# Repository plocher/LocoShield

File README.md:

# LocoShield
## License: CERN Open Hardware Licence v1.2

An electrical interface to Digitrax Loconet

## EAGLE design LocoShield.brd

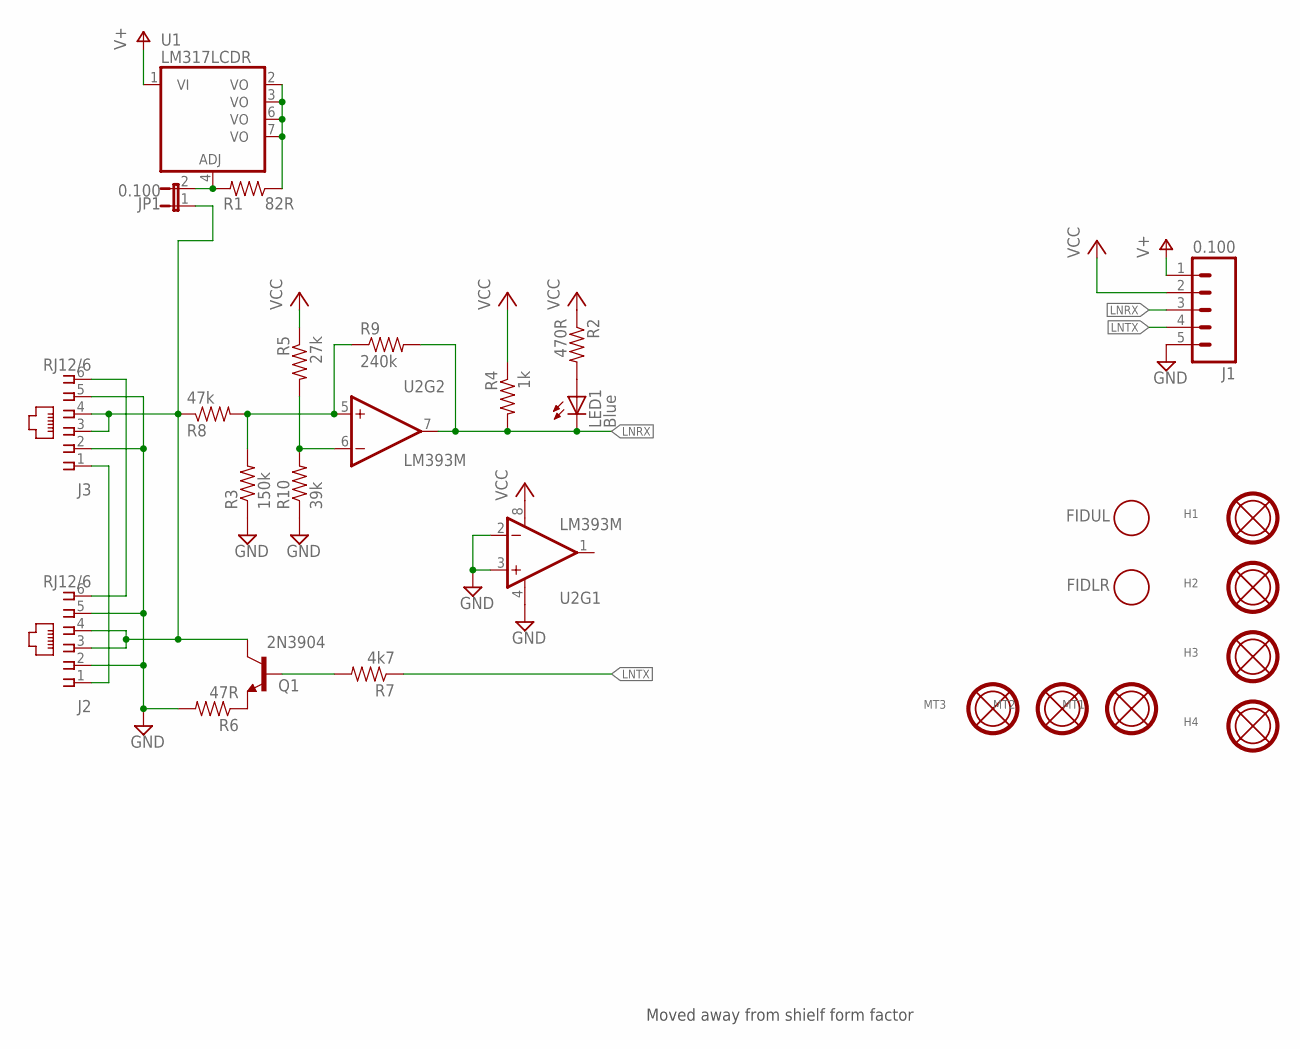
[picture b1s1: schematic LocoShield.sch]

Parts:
FIDLR: FIDUCIAL; FIDUCIAL_1MM
FIDUL: FIDUCIAL; FIDUCIAL_1MM
H1, H2, H3, H4: MOUNTINGHOLEL; MOUNTINGHOLE-L
J1: 0.100; 1X05_LOCK
J2, J3: RJ12/6; RJ25-PANEL
JP1: 0.100; 1X02_LOCK
LED1: Blue; 0603-LED
MT1, MT2, MT3: tool; MOUNTINGHOLE-TOOL
Q1: 2N3904; SOT23
R1: 82R; 0603-RES
R2: 470R; 0603-RES
R3: 150k; 0603-RES
R4: 1k; 0603-RES
R5: 27k; 0603-RES
R6: 47R; 0603-RES
R7: 4k7; 0603-RES
R8: 47k; 0603-RES
R9: 240k; 0603-RES
R10: 39k; 0603-RES
U1: LM317LCDR; SO08
U2: LM393M; SO08

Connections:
DCCRAILSYNC-: J2.1, J3.1
GND: J1.5, J2.2, J2.5, J3.2, J3.5, R3.1, R6.2, R10.1, U2.2 (-IN), U2.3 (+IN), U2.4 (V-)
LNRX: J1.3, LED1.C, R4.2, R9.2, U2.7 (OUT)
LNTX: J1.4, R7.1
LOCONET: J2.3, J2.4, J3.3, J3.4, JP1.1, Q1.3 (C), R8.1
unnamed: Q1.1 (B), R7.2
unnamed: R3.2, R8.2, R9.1, U2.5 (+IN)
unnamed: R5.2, R10.2, U2.6 (-IN)
unnamed: Q1.2 (E), R6.1
unnamed: LED1.A, R2.2
unnamed: JP1.2, R1.2, U1.4 (ADJ)
RAILSYNC+: J2.6, J3.6
V+: J1.1, U1.1 (VI)
VCC: J1.2, R2.1, R4.1, R5.1, U2.8 (V+)
VOUT: R1.1, U1.2 (VO), U1.3 (VO), U1.6 (VO), U1.7 (VO)

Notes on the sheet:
Moved away from shielf form factor

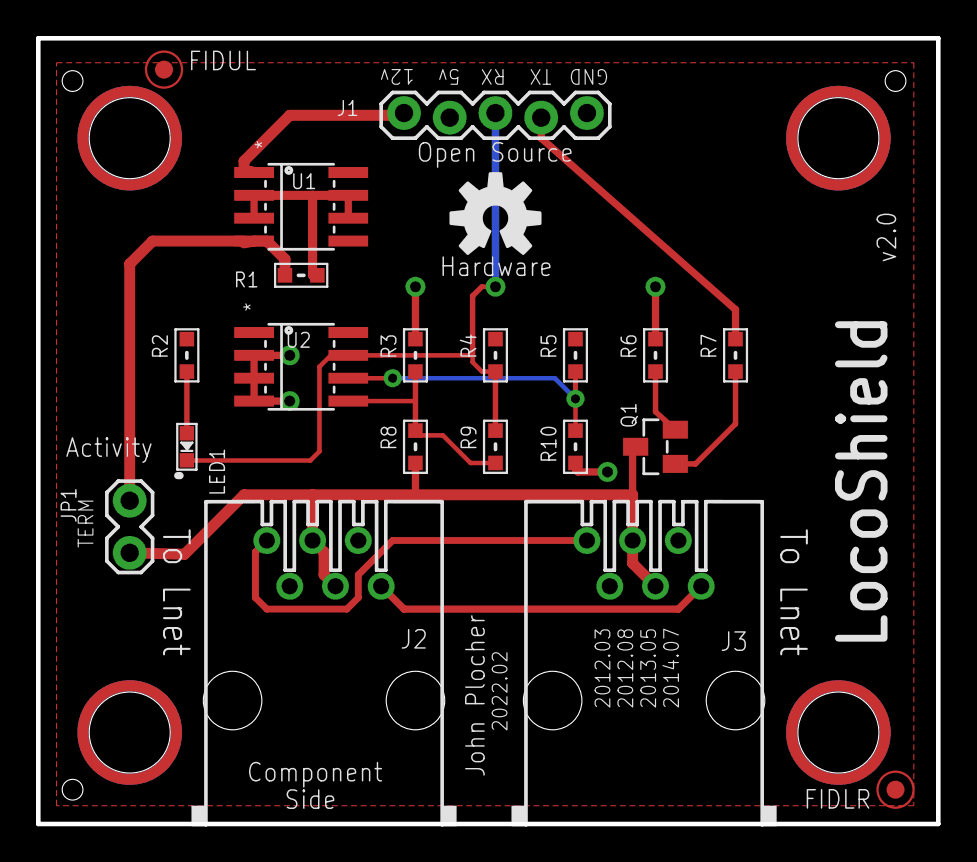
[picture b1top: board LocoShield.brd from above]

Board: 2 copper layers, 50.0 x 43.6 mm, 28 parts (0 on the bottom side), 15 nets.

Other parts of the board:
U$3: OSHW; OSHW-LOGO-M

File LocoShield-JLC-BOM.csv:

Comment,Designator,Footprint,JLCPCB Part #
Blue,LED1,0603-LED,C72041
2N3904,Q1,SOT23,C20526
82R,R1,0603-RES,C23255
470R,R2,0603-RES,C23179
150k,R3,0603-RES,C22807
1k,R4,0603-RES,C21190
27k,R5,0603-RES,C22967
47R,R6,0603-RES,C23182
4k7,R7,0603-RES,C23162
47k,R8,0603-RES,C25819
240k,R9,0603-RES,C4197
39k,R10,0603-RES,C23153
LM317LCDR,U1,SO08,C105219
LM393M,U2,SO08,C7955

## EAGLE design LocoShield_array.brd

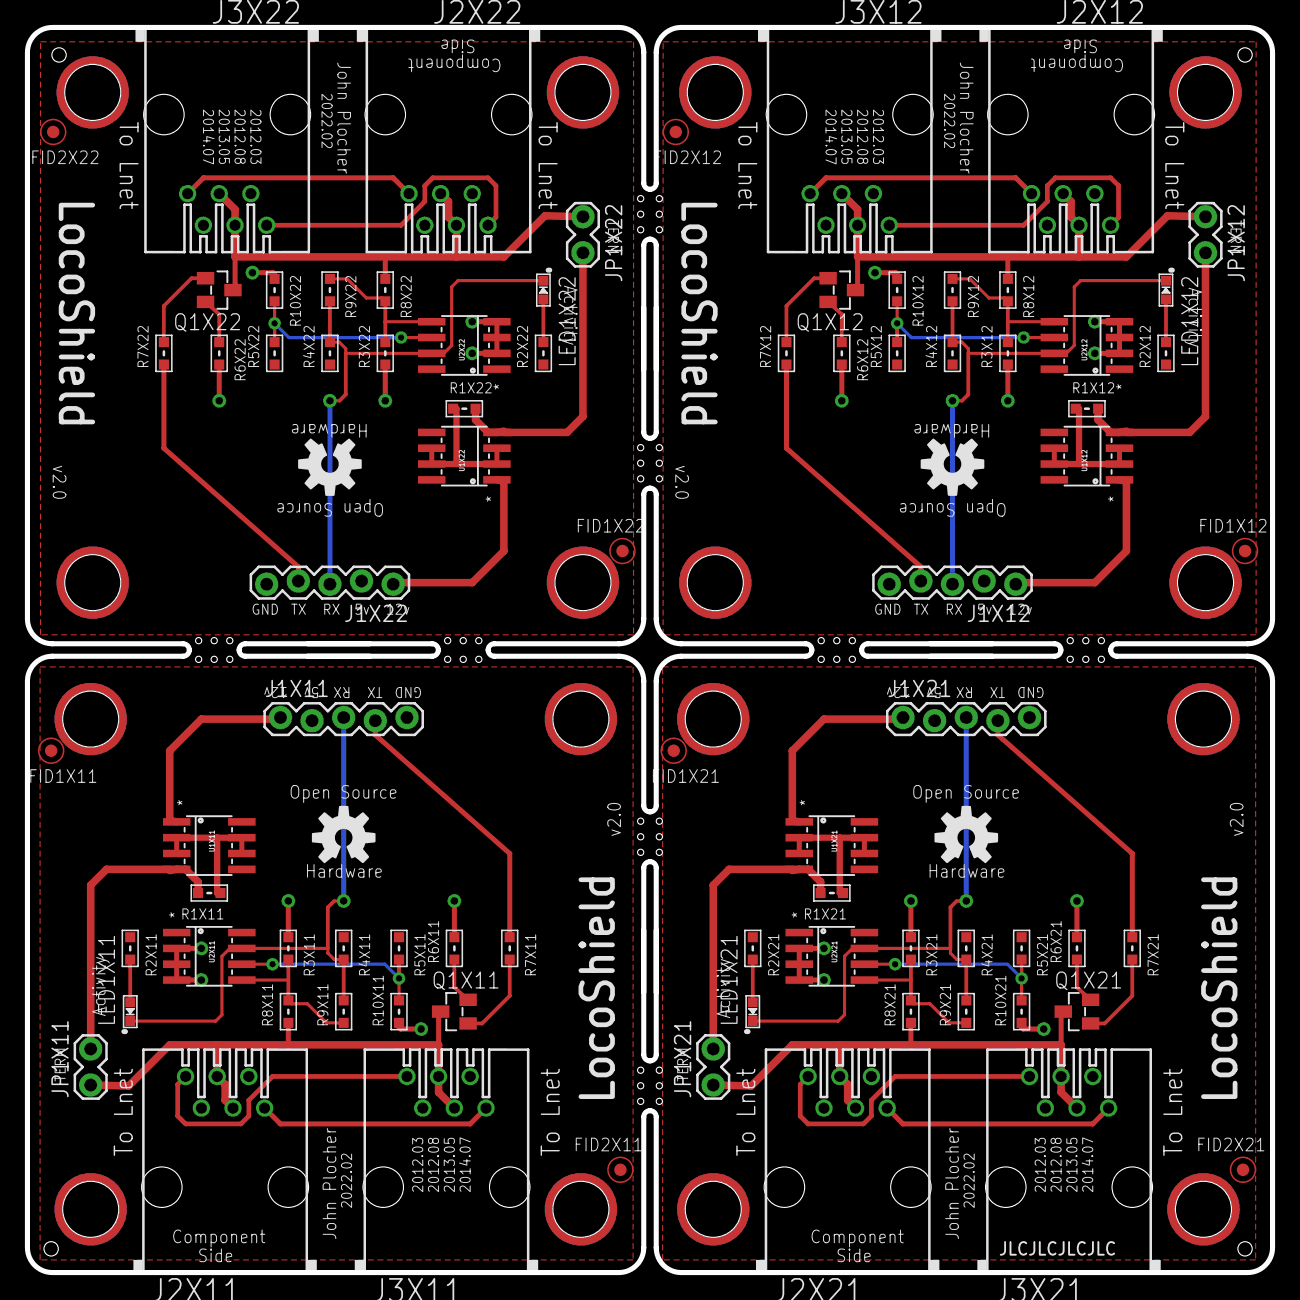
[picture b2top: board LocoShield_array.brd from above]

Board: 2 copper layers, 100.0 x 100.0 mm, 105 parts (0 on the bottom side), 60 nets.

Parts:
FID1X11, FID1X12, FID1X21, FID1X22, FID2X11, FID2X12, FID2X21, FID2X22: FIDUCIAL; FIDUCIAL_1MM
H1X11, H1X12, H1X21, H1X22, H2X11, H2X12, H2X21, H2X22, H3X11, H3X12, H3X21, H3X22, H4X11, H4X12, H4X21, H4X22: MOUNTINGHOLEL; MOUNTINGHOLE-L
J1X11, J1X12, J1X21, J1X22: 0.100; 1X05_LOCK
J2X11, J2X12, J2X21, J2X22, J3X11, J3X12, J3X21, J3X22: RJ12/6; RJ25-PANEL
JP1X11, JP1X12, JP1X21, JP1X22: 0.100; 1X02_LOCK
LED1X11, LED1X12, LED1X21, LED1X22: B; 0603-LED
Q1X11, Q1X12, Q1X21, Q1X22: 2N3904; SOT23
R1X11, R1X12, R1X21, R1X22: 82R; 0603-RES
R2X11, R2X12, R2X21, R2X22: 470R; 0603-RES
R3X11, R3X12, R3X21, R3X22: 150k; 0603-RES
R4X11, R4X12, R4X21, R4X22: 1k; 0603-RES
R5X11, R5X12, R5X21, R5X22: 27k; 0603-RES
R6X11, R6X12, R6X21, R6X22: 47R; 0603-RES
R7X11, R7X12, R7X21, R7X22: 4k7; 0603-RES
R8X11, R8X12, R8X21, R8X22: 47k; 0603-RES
R9X11, R9X12, R9X21, R9X22: 240k; 0603-RES
R10X11, R10X12, R10X21, R10X22: 39k; 0603-RES
U1X11, U1X12, U1X21, U1X22: LM317LCDR; SO08
U2X1: BOARD-10X10-2X2-PANEL-MB
U2X2, U2X3, U2X4, U2X5: MOUNTINGHOLE-TOOL
U2X11, U2X12, U2X21, U2X22: LM393M; SO08
U$3X11, U$3X12, U$3X21, U$3X22: OSHW; OSHW-LOGO-M

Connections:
DCCRAILSYNC-X11: J2X11.1, J3X11.1
DCCRAILSYNC-X12: J2X12.1, J3X12.1
DCCRAILSYNC-X21: J2X21.1, J3X21.1
DCCRAILSYNC-X22: J2X22.1, J3X22.1
GNDX11: J1X11.5, J2X11.2, J2X11.5, J3X11.2, J3X11.5, R3X11.1, R6X11.2, R10X11.1, U2X11.2, U2X11.3, U2X11.4
GNDX12: J1X12.5, J2X12.2, J2X12.5, J3X12.2, J3X12.5, R3X12.1, R6X12.2, R10X12.1, U2X12.2, U2X12.3, U2X12.4
GNDX21: J1X21.5, J2X21.2, J2X21.5, J3X21.2, J3X21.5, R3X21.1, R6X21.2, R10X21.1, U2X21.2, U2X21.3, U2X21.4
GNDX22: J1X22.5, J2X22.2, J2X22.5, J3X22.2, J3X22.5, R3X22.1, R6X22.2, R10X22.1, U2X22.2, U2X22.3, U2X22.4
LNRXX11: J1X11.3, LED1X11.C, R4X11.2, R9X11.2, U2X11.7
LNRXX12: J1X12.3, LED1X12.C, R4X12.2, R9X12.2, U2X12.7
LNRXX21: J1X21.3, LED1X21.C, R4X21.2, R9X21.2, U2X21.7
LNRXX22: J1X22.3, LED1X22.C, R4X22.2, R9X22.2, U2X22.7
LNTXX11: J1X11.4, R7X11.1
LNTXX12: J1X12.4, R7X12.1
LNTXX21: J1X21.4, R7X21.1
LNTXX22: J1X22.4, R7X22.1
LOCONETX11: J2X11.3, J2X11.4, J3X11.3, J3X11.4, JP1X11.1, Q1X11.3, R8X11.1
LOCONETX12: J2X12.3, J2X12.4, J3X12.3, J3X12.4, JP1X12.1, Q1X12.3, R8X12.1
LOCONETX21: J2X21.3, J2X21.4, J3X21.3, J3X21.4, JP1X21.1, Q1X21.3, R8X21.1
LOCONETX22: J2X22.3, J2X22.4, J3X22.3, J3X22.4, JP1X22.1, Q1X22.3, R8X22.1
unnamed: Q1X11.1, R7X11.2
unnamed: Q1X12.1, R7X12.2
unnamed: Q1X21.1, R7X21.2
unnamed: Q1X22.1, R7X22.2
unnamed: R3X11.2, R8X11.2, R9X11.1, U2X11.5
unnamed: R3X12.2, R8X12.2, R9X12.1, U2X12.5
unnamed: R3X21.2, R8X21.2, R9X21.1, U2X21.5
unnamed: R3X22.2, R8X22.2, R9X22.1, U2X22.5
unnamed: R5X11.2, R10X11.2, U2X11.6
unnamed: R5X12.2, R10X12.2, U2X12.6
unnamed: R5X21.2, R10X21.2, U2X21.6
unnamed: R5X22.2, R10X22.2, U2X22.6
unnamed: Q1X11.2, R6X11.1
unnamed: Q1X12.2, R6X12.1
unnamed: Q1X21.2, R6X21.1
unnamed: Q1X22.2, R6X22.1
unnamed: LED1X11.A, R2X11.2
unnamed: LED1X12.A, R2X12.2
unnamed: LED1X21.A, R2X21.2
unnamed: LED1X22.A, R2X22.2
unnamed: JP1X11.2, R1X11.2, U1X11.4
unnamed: JP1X12.2, R1X12.2, U1X12.4
unnamed: JP1X21.2, R1X21.2, U1X21.4
unnamed: JP1X22.2, R1X22.2, U1X22.4
RAILSYNC+X11: J2X11.6, J3X11.6
RAILSYNC+X12: J2X12.6, J3X12.6
RAILSYNC+X21: J2X21.6, J3X21.6
RAILSYNC+X22: J2X22.6, J3X22.6
V+X11: J1X11.1, U1X11.1
V+X12: J1X12.1, U1X12.1
V+X21: J1X21.1, U1X21.1
V+X22: J1X22.1, U1X22.1
VCCX11: J1X11.2, R2X11.1, R4X11.1, R5X11.1, U2X11.8
VCCX12: J1X12.2, R2X12.1, R4X12.1, R5X12.1, U2X12.8
VCCX21: J1X21.2, R2X21.1, R4X21.1, R5X21.1, U2X21.8
VCCX22: J1X22.2, R2X22.1, R4X22.1, R5X22.1, U2X22.8
VOUTX11: R1X11.1, U1X11.2, U1X11.3, U1X11.6, U1X11.7
VOUTX12: R1X12.1, U1X12.2, U1X12.3, U1X12.6, U1X12.7
VOUTX21: R1X21.1, U1X21.2, U1X21.3, U1X21.6, U1X21.7
VOUTX22: R1X22.1, U1X22.2, U1X22.3, U1X22.6, U1X22.7

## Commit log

2019-12-09 added graphic
2020-05-04 updated tags
2020-10-05 added missing values
2020-10-06 normalized values
2022-02-20 moved away from shield form
2022-02-20 fixed silk layout
2022-02-20 Version 2.0
2022-02-23 Updated to match v2.0 board
2022-02-23 added tooling for JLC
2022-02-23 vscore->mousebites
2022-02-23 added JLC fab files
